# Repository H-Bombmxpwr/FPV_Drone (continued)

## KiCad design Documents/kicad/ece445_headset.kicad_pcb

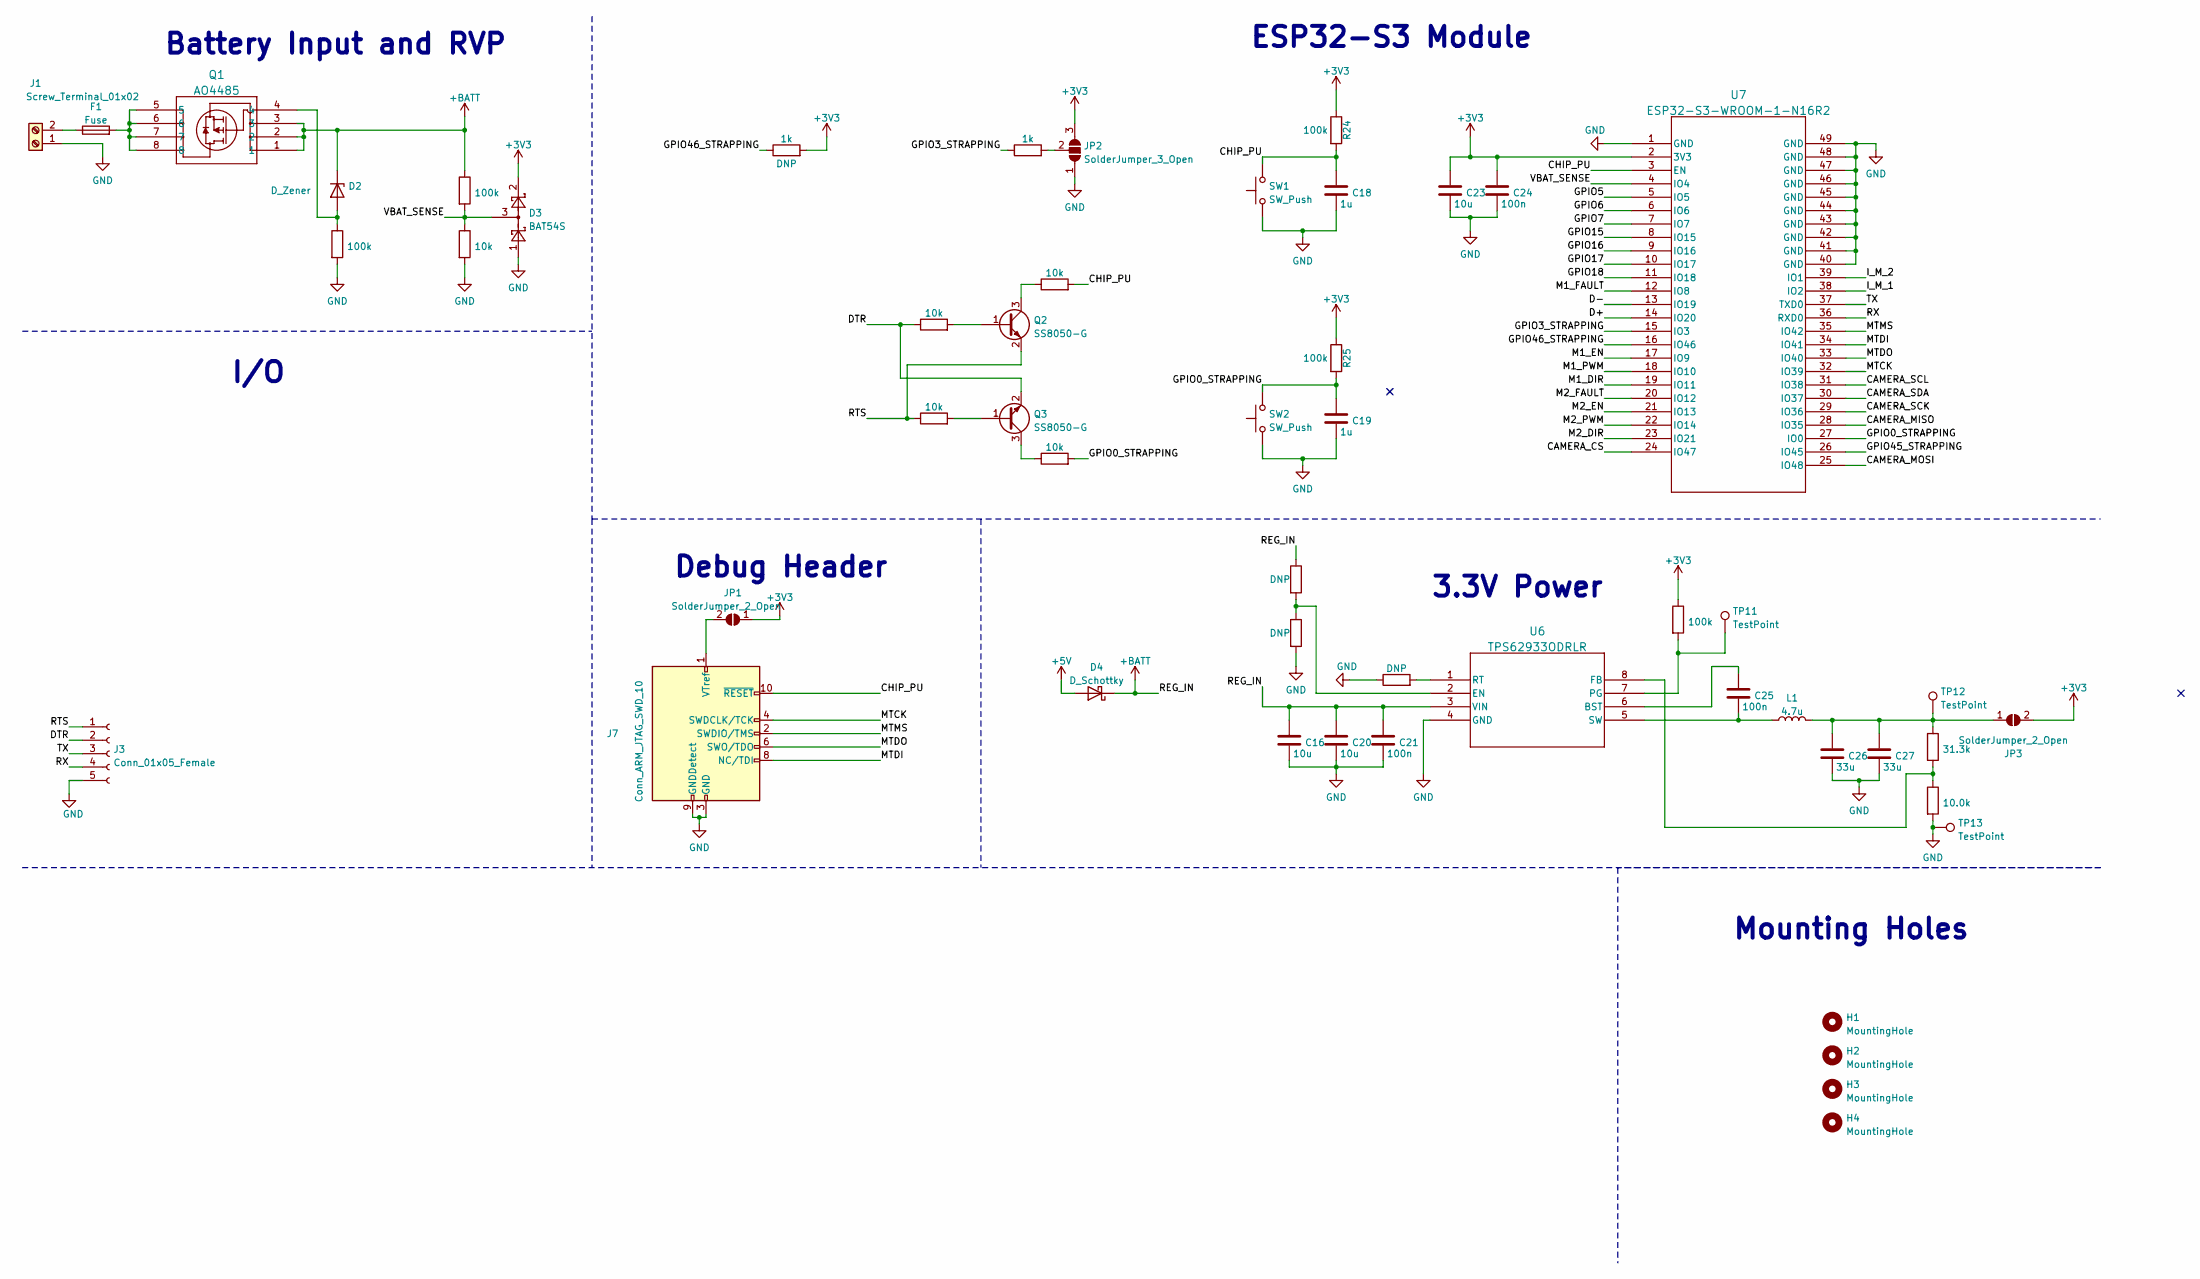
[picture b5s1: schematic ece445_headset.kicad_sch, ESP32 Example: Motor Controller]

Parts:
C16, C20, C23: 10u; C_0805_2012Metric
C18, C19: 1u; C_0805_2012Metric
C21, C24, C25: 100n; C_0805_2012Metric
C26, C27: 33u; C_0805_2012Metric
D2: D_Zener; SOD-123_ONS
D3: BAT54S; SOT-23
D4: D_Schottky; D_SMA
F1: Fuse; Fuseholder_Littelfuse_Nano2_154x
H1, H2, H3, H4: MountingHole; MountingHole_3.2mm_M3
J1: Screw_Terminal_01x02; TerminalBlock_Phoenix_MKDS-1,5-2-5.08_1x02_P5.08mm_Horizont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
J3: Conn_01x05_Female; PinHeader_1x05_P2.54mm_Vertical
J7: Conn_ARM_JTAG_SWD_10; IDC-Header_2x05_P2.54mm_Vertical
JP1, JP3: SolderJumper_2_Open; SolderJumper-2_P1.3mm_Open_TrianglePad1.0x1.5mm
JP2: SolderJumper_3_Open; SolderJumper-3_P2.0mm_Open_TrianglePad1.0x1.5mm
L1: 4.7u; L_Taiyo-Yuden_NR-60xx
Q1: AO4485; SO8SOP-8L_AOS
Q2, Q3: SS8050-G; SOT-23
R6, R8, R24, R25, R29: 100k; R_0805_2012Metric
R9, R13, R14, R18, R19: 10k; R_0805_2012Metric
R12, R17: 1k; R_0805_2012Metric
R22, R23, R26: DNP; R_0805_2012Metric
R30: 31.3k; R_0805_2012Metric
R31: 10.0k; R_0805_2012Metric
SW1, SW2: SW_Push; SW_SPST_B3S-1000
TP11: TestPoint; TestPoint_Pad_D2.0mm
TP12, TP13: TestPoint; TestPoint_Keystone_5010-5014_Multipurpose
U6: TPS62933ODRLR; SOT5X3-8_DRL_TEX
U7: ESP32-S3-WROOM-1-N16R2; ESP32-S3-WROOM-1_EXP

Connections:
+3V3: C23.1, C24.1, D3.2, JP1.1 (A), JP2.3 (B), JP3.2 (B), R12.2, R24.1, R25.1, R29.1, U7.2 (3V3)
+5V: D4.2 (A)
+BATT: C16.1, C20.1, C21.1, D2.1 (K), D4.1 (K), Q1.1, Q1.2, Q1.3, R8.1, R22.1, U6.3 (VIN)
/CAMERA_CS: U7.24 (IO47)
/CAMERA_MISO: U7.28 (IO35)
/CAMERA_MOSI: U7.25 (IO48)
/CAMERA_SCK: U7.29 (IO36)
/CAMERA_SCL: U7.31 (IO38)
/CAMERA_SDA: U7.30 (IO37)
/CHIP_PU: C18.1, J7.10 (~RESET), R18.2, R24.2, SW1.2, U7.3 (EN)
/D+: U7.14 (IO20)
/D-: U7.13 (IO19)
/DTR: J3.2, Q3.2 (E), R13.1
/GPIO0_STRAPPING: C19.1, R19.2, R25.2, SW2.2, U7.27 (IO0)
/GPIO3_STRAPPING: R17.1, U7.15 (IO3)
/GPIO5: U7.5 (IO5)
/GPIO6: U7.6 (IO6)
/GPIO7: U7.7 (IO7)
/GPIO15: U7.8 (IO15)
/GPIO16: U7.9 (IO16)
/GPIO17: U7.10 (IO17)
/GPIO18: U7.11 (IO18)
/GPIO45_STRAPPING: U7.26 (IO45)
/GPIO46_STRAPPING: R12.1, U7.16 (IO46)
/I_M_1: U7.38 (IO2)
/I_M_2: U7.39 (IO1)
/M1_DIR: U7.19 (IO11)
/M1_EN: U7.17 (IO9)
/M1_FAULT: U7.12 (IO8)
/M1_PWM: U7.18 (IO10)
/M2_DIR: U7.23 (IO21)
/M2_EN: U7.21 (IO13)
/M2_FAULT: U7.20 (IO12)
/M2_PWM: U7.22 (IO14)
/MTCK: J7.4 (SWDCLK/TCK), U7.32 (IO39)
/MTDI: J7.8 (NC/TDI), U7.34 (IO41)
/MTDO: J7.6 (SWO/TDO), U7.33 (IO40)
/MTMS: J7.2 (SWDIO/TMS), U7.35 (IO42)
/RTS: J3.1, Q2.2 (E), R14.1
/RX: J3.4, U7.36 (RXD0)
/TX: J3.3, U7.37 (TXD0)
/VBAT_SENSE: D3.3, R8.2, R9.1, U7.4 (IO4)
GND: C16.2, C18.2, C19.2, C20.2, C21.2, C23.2, C24.2, C26.2, C27.2, D3.1, J1.1, J3.5, J7.3 (GND), J7.5 (GND), J7.9 (GNDDetect), JP2.1 (A), R6.2, R9.2, R23.2, R26.1, R31.2, SW1.1, SW2.1, TP13.1, U6.4 (GND), U7.1 (GND), U7.40 (GND), U7.41 (GND), U7.42 (GND), U7.43 (GND), U7.44 (GND), U7.45 (GND), U7.46 (GND), U7.47 (GND), U7.48 (GND), U7.49 (GND)
unnamed: D2.2 (A), Q1.4, R6.1
unnamed: F1.2, Q1.5, Q1.6, Q1.7, Q1.8
unnamed: F1.1, J1.2
unnamed: J7.1 (VTref), JP1.2 (B)
unnamed: JP2.2 (C), R17.2
unnamed: C26.1, C27.1, JP3.1 (A), L1.2, R30.1, TP12.1
unnamed: Q2.1 (B), R13.2
unnamed: Q2.3 (C), R18.1
unnamed: Q3.1 (B), R14.2
unnamed: Q3.3 (C), R19.1
unnamed: C25.1, U6.6 (BST)
unnamed: R22.2, R23.1, U6.2 (EN)
unnamed: R30.2, R31.1, U6.8 (FB)
unnamed: R29.2, TP11.1, U6.7 (PG)
unnamed: R26.2, U6.1 (RT)
unnamed: C25.2, L1.1, U6.5 (SW)

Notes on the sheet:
ESP32-S3 Module
Debug Header
Mounting Holes
3.3V Power
Battery Input and RVP
I/O

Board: 2 copper layers, 52 parts (0 on the bottom side), 32 nets, no tracks yet.

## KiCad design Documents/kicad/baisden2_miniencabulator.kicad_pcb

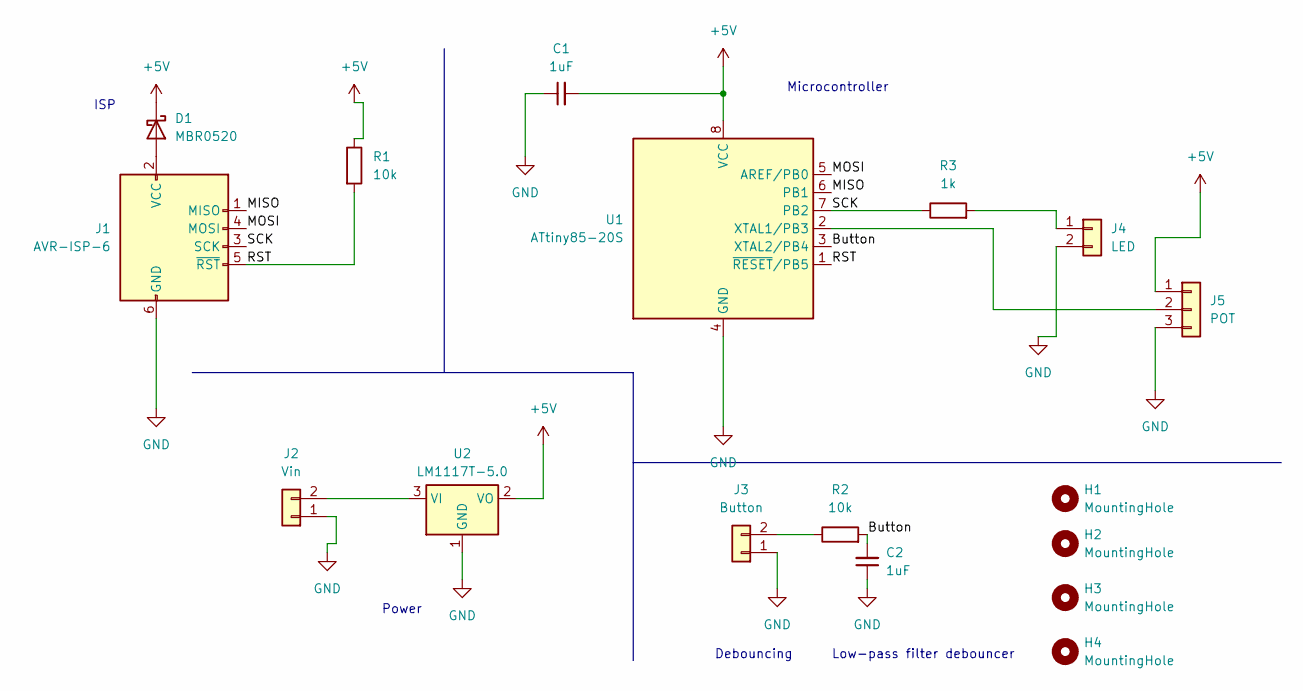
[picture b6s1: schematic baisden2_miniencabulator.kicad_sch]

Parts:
C1, C2: 1uF; C_0805_2012Metric_Pad1.18x1.45mm_HandSolder
D1: MBR0520; D_SOD-123
H1, H2, H3, H4: MountingHole; MountingHole_3.2mm_M3
J1: AVR-ISP-6; IDC-Header_2x03_P2.54mm_Vertical
J2: Vin; Molex_KK-254_AE-6410-02A_1x02_P2.54mm_Vertical
J3: Button; Molex_KK-254_AE-6410-02A_1x02_P2.54mm_Vertical
J4: LED; Molex_KK-254_AE-6410-02A_1x02_P2.54mm_Vertical
J5: POT; Molex_KK-254_AE-6410-03A_1x03_P2.54mm_Vertical
R1, R2: 10k; R_0805_2012Metric_Pad1.20x1.40mm_HandSolder
R3: 1k; R_0805_2012Metric_Pad1.20x1.40mm_HandSolder
U1: ATtiny85-20S; SOIC-8W_5.3x5.3mm_P1.27mm
U2: LM1117T-5.0; SOT-223

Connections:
+5V: C1.2, D1.1 (K), J5.1, R1.1, U1.8 (VCC), U2.2 (VO)
/Button: C2.2, R2.2, U1.3 (XTAL2/PB4)
/MISO: J1.1 (MISO), U1.6 (PB1)
/MOSI: J1.4 (MOSI), U1.5 (AREF/PB0)
/RST: J1.5 (~RST), R1.2, U1.1 (~RESET/PB5)
/SCK: J1.3 (SCK), R3.1, U1.7 (PB2)
GND: C1.1, C2.1, J1.6 (GND), J2.1, J3.1, J4.2, J5.3, U1.4 (GND), U2.1 (GND)
unnamed: D1.2 (A), J1.2 (VCC)
unnamed: J2.2, U2.3 (VI)
unnamed: J3.2, R2.1
unnamed: J4.1, R3.2
unnamed: J5.2, U1.2 (XTAL1/PB3)

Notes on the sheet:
ISP
Microcontroller
Low-pass filter debouncer
Debouncing
Power

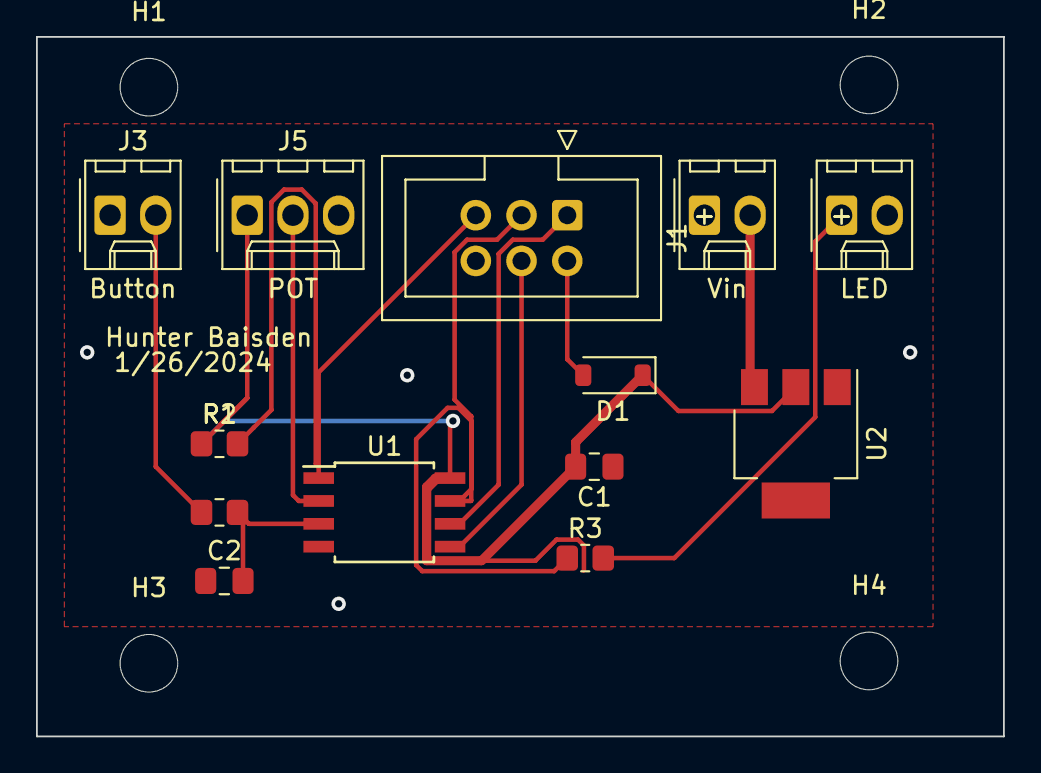
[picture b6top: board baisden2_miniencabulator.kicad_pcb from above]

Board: 2 copper layers, 53.7 x 38.9 mm, 17 parts (0 on the bottom side), 12 nets.

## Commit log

2024-02-06 adding placeholders
2024-02-06 adding more files
2024-02-06 fixes
2024-02-13 block diagram added
2024-02-21 push
2024-02-27 adding design document
2024-03-01 crazyflie
2024-03-01 adding requirements
2024-03-01 precommint
2024-03-01 clientside
2024-03-01 more changes
2024-03-01 locker
2024-03-01 file
2024-03-27 Create temp
2024-03-29 Adding Current Draft of LED Circuit Schematic
2024-03-31 new stuff
2024-03-31 adapter board changes
2024-03-31 adding LEd footprint
2024-03-31 schematic finished
2024-03-31 finished board
2024-04-01 adding gerber files
2024-04-01 directory changes
2024-04-01 more zip
2024-04-01 sending zip
2024-04-02 extracting headset zip
2024-04-02 LED Gerbers Griffin - Post Audit
2024-04-02 LED Circuit Kicad Griffin - Post Audit
2024-04-02 small changes
2024-04-05 control changes
2024-04-05 requirements change
2024-04-05 readme changes
2024-04-05 adding firmware
2024-04-07 Create empty
2024-04-08 reflashed crazyflie
2024-04-08 new headset board
2024-04-09 visuals for adapter board
2024-04-10 Adding updated LED PCBs
2024-04-11 md changes
2024-04-13 webserver code for griffin
2024-04-17 LED Circuit with pushbutton
2024-04-17 Circuit with switches
2024-04-30 adding stuff
2024-05-01 final presentation
2024-05-01 markdown changes
2024-05-02 adding final report
2024-05-02 readme
2024-05-03 Code updates
2024-05-03 adding new code
2024-05-03 hunter readme
2024-05-03 small delete
